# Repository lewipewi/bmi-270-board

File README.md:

# bmi-270 board

Compact wireless 6-axis motion sensor board. Single-cell LiPo or USB powered,
with USB-serial for flashing and debug. Part of a larger project aimed at playing fighting games using the body.

## Hardware

| Part | Function |
|------|----------|
| ESP32-C3-MINI-1-N4 | RISC-V MCU, 4 MB flash, Wi-Fi + BLE |
| BMI270 | 6-axis IMU (accel + gyro), I²C @ 0x68 |
| AP2112K-3.3 | 600 mA LDO |
| CH343P | USB-serial bridge |
| SS-12D00-G3 | SPDT slide switch — selects VBAT or VBUS as LDO input |
| JST-PH 2-pin | Battery input (no onboard charger) |

2-layer, ~40 × 42 mm. Module antenna overhangs the board edge.

*3D View*

## Notes

- **No auto-reset.** CH343P DTR/RTS are unconnected. To flash: hold SW1, tap SW2,
  release SW1.
- **No native USB.** IO18/IO19 are used for LEDs, so USB-CDC and USB-JTAG are
  unavailable. All flashing and console goes through the CH343P.
- **No charger.** Cells must be charged externally. LDO dropout puts the practical
  low-battery cutoff around 3.6 V.
- **No reverse-polarity protection** on the battery connector. Verify cell polarity
  against CN1 (pin 1 = +) before connecting.

## Status

Board 1 assembled and under test.

- [x] Pre-power continuity checks
- [x] 3.3 V rail up
- [x] USB enumerates (CH343P)
- [ ] ROM boot log
- [ ] Flash / firmware
- [ ] IMU bring-up

### Rework log (board 1)

- One USB-C CC pin had a cold joint — board only powered with the cable in one
  orientation. Reflow CC1/CC2.
- D2 not conducting; 3.3 V rail dead until reworked.

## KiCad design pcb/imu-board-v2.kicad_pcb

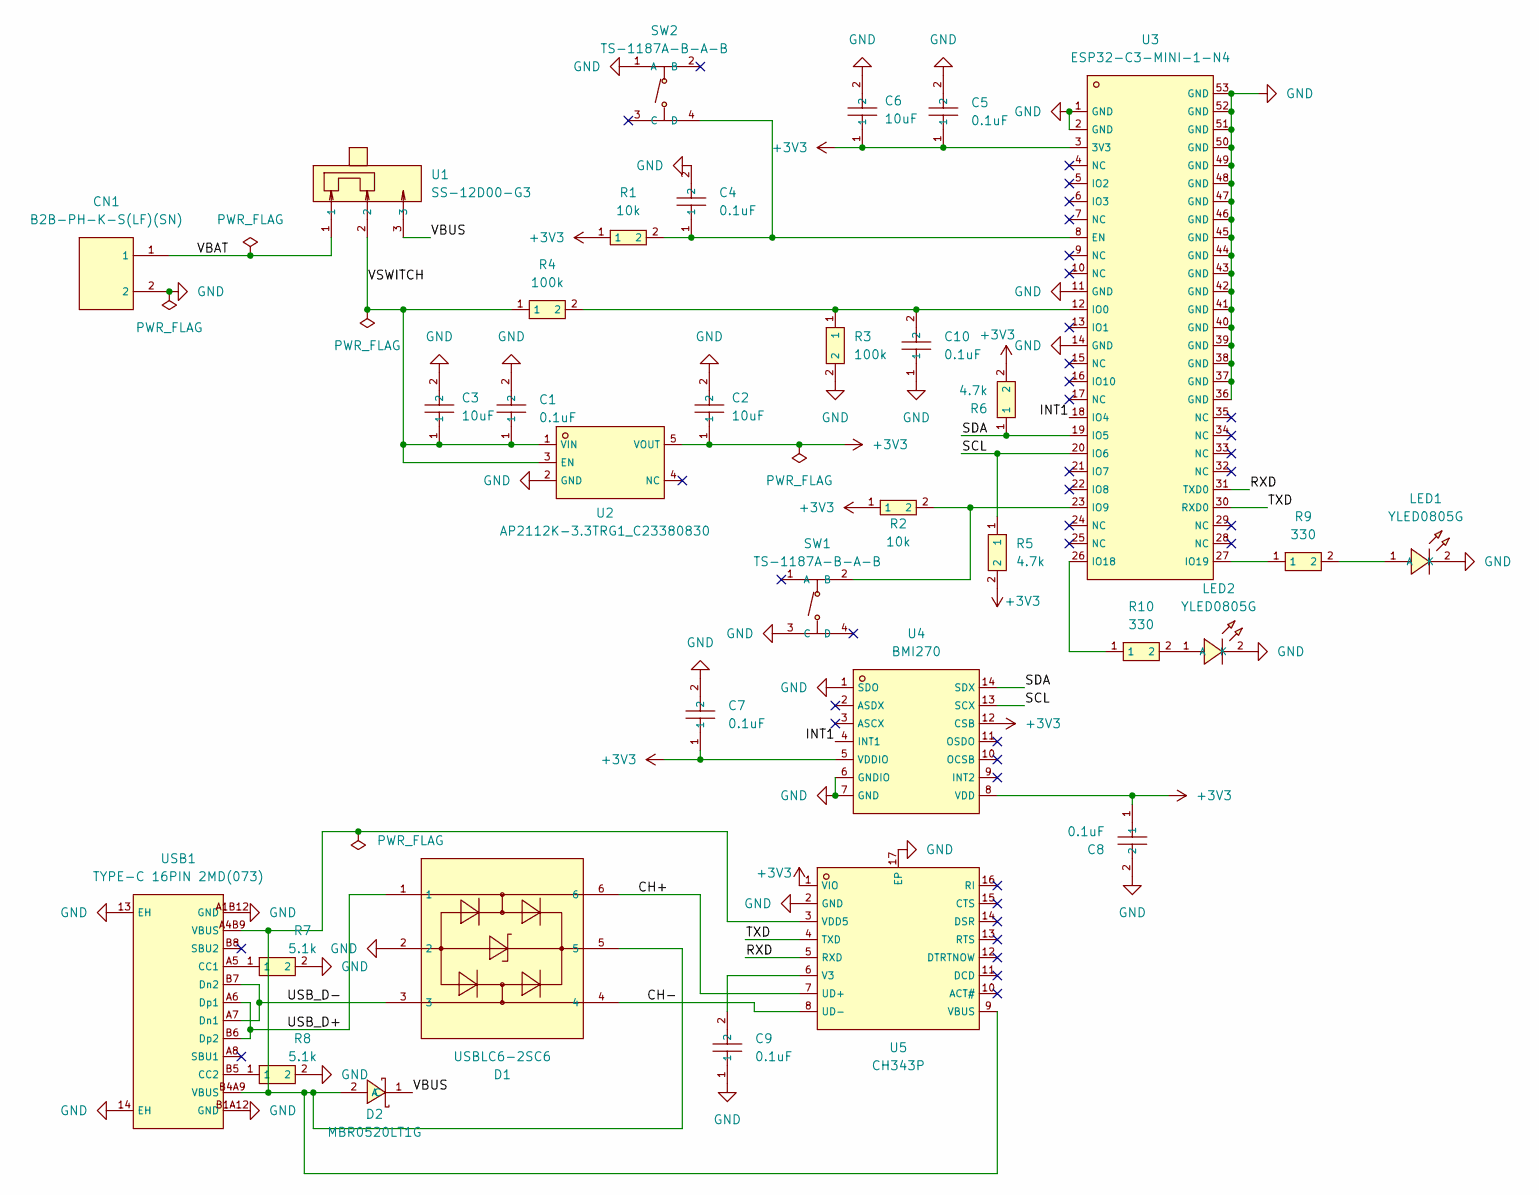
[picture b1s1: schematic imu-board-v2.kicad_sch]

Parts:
C1, C4, C5, C7, C8, C9, C10: 0.1uF; C1591_C0603; LCSC C1591
C2, C3, C6: 10uF; C318691_C0805; LCSC C318691
CN1: B2B-PH-K-S(LF)(SN); C131337_CONN-TH_B2B-PH-K-S; LCSC C131337
D1: USBLC6-2SC6; C7519_SOT-23-6_L2_9-W1_6-P0_95-LS2_8-BL; LCSC C7519
D2: MBR0520LT1G; C23848_SOD-123_L2_8-W1_8-LS3_7-RD; LCSC C23848
LED1, LED2: YLED0805G; C25170728_LED0805-FD-GREEN; LCSC C25170728
R1, R2: 10k; C95204_R0603; LCSC C95204
R3, R4: 100k; C2906980_R0603; LCSC C2906980
R5, R6: 4.7k; C2907034_R0603; LCSC C2907034
R7, R8: 5.1k; C2907044_R0603; LCSC C2907044
R9, R10: 330; C2933198_R0603; LCSC C2933198
SW1, SW2: TS-1187A-B-A-B; C318884_SW-SMD_4P-L5_1-W5_1-P3_70-LS6_5-TL_H1_5; LCSC C318884
U1: SS-12D00-G3; C22355741_SW-TH_3P-L8_8-W3_9-P2_50_SS12D00G3; LCSC C22355741
U2: AP2112K-3.3TRG1_C23380830; C23380830_SOT-23-5_L2_9-W1_6-P0_95-LS2_8-BR; LCSC C23380830
U3: ESP32-C3-MINI-1-N4; C2838502_WIFIM-SMD_ESP32-C3-MINI-1; LCSC C2838502
U4: BMI270; C2836813_LGA-14_L3_0-W2_5-P0_50-BR; LCSC C2836813
U5: CH343P; C2846043_TQFN-16_L3_0-W3_0-P0_50-BL-EP1_7; LCSC C2846043
USB1: TYPE-C 16PIN 2MD(073); C2765186_USB-C-SMD_TYPE-C-16PIN-2MD-073; LCSC C2765186

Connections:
+3V3: C2.1, C5.1, C6.1, C7.1, C8.1, R1.1, R2.1, R5.2, R6.2, U2.5 (VOUT), U3.3 (3V3), U4.5 (VDDIO), U4.8 (VDD), U4.12 (CSB), U5.1 (VIO)
/CH+: D1.6, U5.7 (UD+)
/CH-: D1.4, U5.8 (UD-)
/INT1: U3.18 (IO4), U4.4 (INT1)
/RXD: U3.31 (TXD0), U5.5 (RXD)
/SCL: R5.1, U3.20 (IO6), U4.13 (SCX)
/SDA: R6.1, U3.19 (IO5), U4.14 (SDX)
/TXD: U3.30 (RXD0), U5.4 (TXD)
/USB_D+: D1.1, USB1.A6 (Dp1), USB1.B6 (Dp2)
/USB_D-: D1.3, USB1.A7 (Dn1), USB1.B7 (Dn2)
/VBAT: CN1.1, U1.1
/VBUS: D2.1 (C), U1.3
/VSWITCH: C1.1, C3.1, R4.1, U1.2, U2.1 (VIN), U2.3 (EN)
GND: C1.2, C2.2, C3.2, C4.2, C5.2, C6.2, C7.2, C8.2, C9.1, C10.1, CN1.2, D1.2, LED1.2 (K), LED2.2 (K), R3.2, R7.2, R8.2, SW1.3 (C), SW2.1 (A), U2.2 (GND), U3.1 (GND), U3.2 (GND), U3.11 (GND), U3.14 (GND), U3.36 (GND), U3.37 (GND), U3.38 (GND), U3.39 (GND), U3.40 (GND), U3.41 (GND), U3.42 (GND), U3.43 (GND), U3.44 (GND), U3.45 (GND), U3.46 (GND), U3.47 (GND), U3.48 (GND), U3.49 (GND), U3.50 (GND), U3.51 (GND), U3.52 (GND), U3.53 (GND), U4.1 (SDO), U4.6 (GNDIO), U4.7 (GND), U5.2 (GND), U5.17 (EP), USB1.13 (EH), USB1.14 (EH), USB1.A1B12 (GND), USB1.B1A12 (GND)
unnamed: D1.5, D2.2 (A), U5.3 (VDD5), U5.9 (VBUS), USB1.A4B9 (VBUS), USB1.B4A9 (VBUS)
unnamed: LED1.1 (A), R9.2
unnamed: LED2.1 (A), R10.2
unnamed: R2.2, SW1.2 (B), U3.23 (IO9)
unnamed: C4.1, R1.2, SW2.4 (D), U3.8 (EN)
unnamed: C10.2, R3.1, R4.2, U3.12 (IO0)
unnamed: R10.1, U3.26 (IO18)
unnamed: R9.1, U3.27 (IO19)
unnamed: C9.2, U5.6 (V3)
unnamed: R7.1, USB1.A5 (CC1)
unnamed: R8.1, USB1.B5 (CC2)

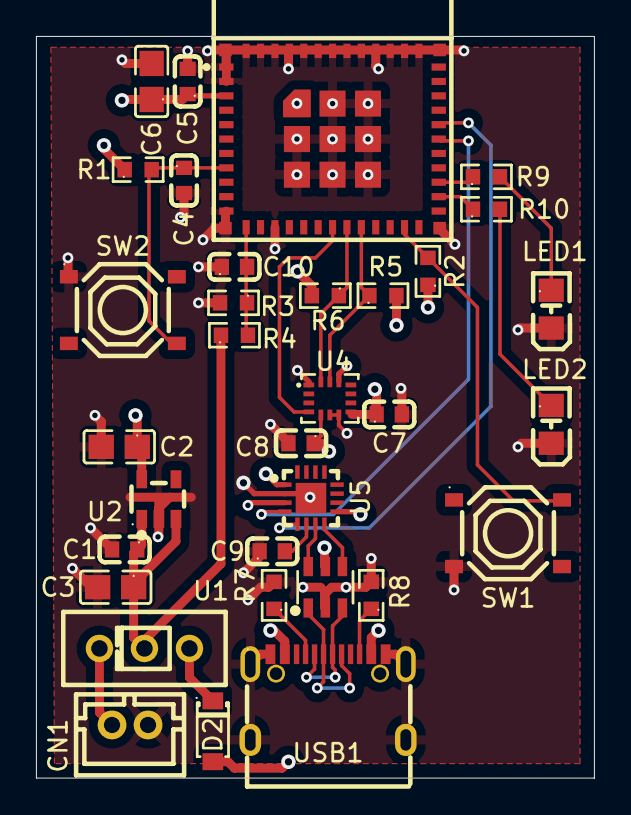
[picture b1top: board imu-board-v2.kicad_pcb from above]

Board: 4 copper layers, 31.0 x 41.2 mm, 33 parts (0 on the bottom side), 25 nets.
